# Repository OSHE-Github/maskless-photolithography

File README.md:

# Maskless Photolithography

*･゜ﾟ･*:.｡..｡.:*･'(*ﾟ▽ﾟ*)'･*:.｡. .｡.:*･゜ﾟ･*

## Copyright

- All code is licensed under the GPL 3.0 or later. You can view a copy of this license in LICENSE.code
- All hardware computer aided design "CAD files" are licensed under the CERN-OHL-S license. A copy of this license can be found in LICENSE.cad
- Some footprints are provided by the manufacturer or a third party source. They are licensed under their respective licenses.

Which licenses apply to which files will be clarified in a later commit. If you have questions please contact us.

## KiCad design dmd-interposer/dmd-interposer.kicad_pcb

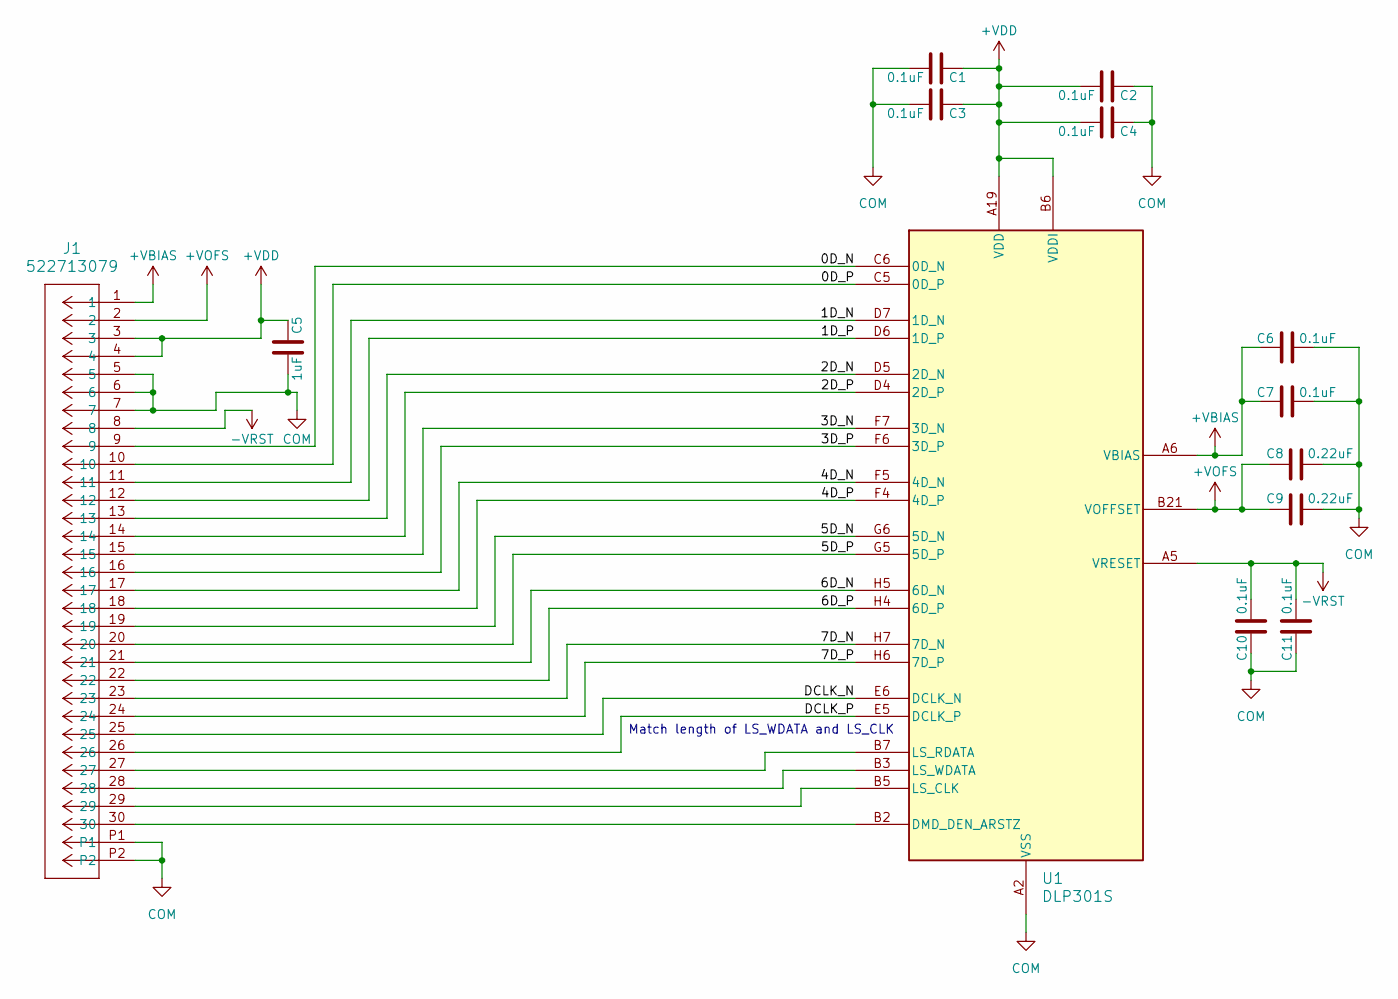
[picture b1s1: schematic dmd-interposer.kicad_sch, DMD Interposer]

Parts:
C1, C2, C3, C4, C6, C7, C10, C11: 0.1uF; C_0603_1608Metric_Pad1.08x0.95mm_HandSolder; Digikey 4713-GMC10X7R104K50NTCT-ND
C5: 1uF; C_0603_1608Metric_Pad1.08x0.95mm_HandSolder; Digikey 1276-1946-1-ND
C8, C9: 0.22uF; C_0805_2012Metric_Pad1.18x1.45mm_HandSolder; Digikey 1276-CL21B224KBFNNNFCT-ND
J1: 522713079; CON_522713079_MOL
U1: DLP301S; PCB_OUTLINE_DLP301S_INTERPOSER

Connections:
+VBIAS: C6.1, C7.1, J1.1, U1.A6 (VBIAS), U1.A22 (VBIAS)
+VDD: C1.1, C2.2, C3.1, C4.2, C5.1, J1.3, J1.4, U1.A19 (VDD), U1.A20 (VDD), U1.A21 (VDD), U1.B6 (VDDI), U1.B19 (VDDI), U1.B20 (VDD), U1.C2 (VDD), U1.C3 (VDDI), U1.C23 (VDDI), U1.D2 (VDD), U1.D3 (VDD), U1.D23 (VDD), U1.E2 (VDD), U1.E3 (VDDI), U1.E23 (VDDI), U1.F2 (VDD), U1.F3 (VDD), U1.F23 (VDD), U1.G3 (VDDI), U1.G23 (VDDI)
+VOFS: C8.2, C9.2, J1.2, U1.B21 (VOFFSET), U1.G2 (VOFFSET)
-VRST: C10.2, C11.2, J1.8, U1.A5 (VRESET), U1.A23 (VRESET)
/0D_N: J1.9, U1.C6 (0D_N)
/0D_P: J1.10, U1.C5 (0D_P)
/1D_N: J1.11, U1.D7 (1D_N)
/1D_P: J1.12, U1.D6 (1D_P)
/2D_N: J1.13, U1.D5 (2D_N)
/2D_P: J1.14, U1.D4 (2D_P)
/3D_N: J1.15, U1.F7 (3D_N)
/3D_P: J1.16, U1.F6 (3D_P)
/4D_N: J1.17, U1.F5 (4D_N)
/4D_P: J1.18, U1.F4 (4D_P)
/5D_N: J1.19, U1.G6 (5D_N)
/5D_P: J1.20, U1.G5 (5D_P)
/6D_N: J1.21, U1.H5 (6D_N)
/6D_P: J1.22, U1.H4 (6D_P)
/7D_N: J1.23, U1.H7 (7D_N)
/7D_P: J1.24, U1.H6 (7D_P)
/DCLK_N: J1.25, U1.E6 (DCLK_N)
/DCLK_P: J1.26, U1.E5 (DCLK_P)
COM: C1.2, C2.1, C3.2, C4.1, C5.2, C6.2, C7.2, C8.1, C9.1, C10.1, C11.1, J1.5, J1.6, J1.7, J1.P1, J1.P2, U1.A2 (VSS), U1.A3 (VSS), U1.A4 (VSS), U1.A7 (VSS), U1.A24 (VSS), U1.B22 (VSS), U1.B23 (VSS), U1.B24 (VSS), U1.C4 (VSS), U1.C7 (VSS), U1.C19 (VSS), U1.C22 (VSS), U1.E4 (VSS), U1.E7 (VSS), U1.E19 (VSS), U1.E22 (VSS), U1.G4 (VSS), U1.G7 (VSS), U1.G19 (VSS), U1.G22 (VSS), U1.G24 (VSS), U1.H2 (VSS), U1.H3 (VSS), U1.H23 (VSS), U1.H24 (VSS)
unnamed: J1.30, U1.B2 (DMD_DEN_ARSTZ)
unnamed: J1.29, U1.B5 (LS_CLK)
unnamed: J1.27, U1.B7 (LS_RDATA)
unnamed: J1.28, U1.B3 (LS_WDATA)

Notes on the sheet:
Match length of LS_WDATA and LS_CLK

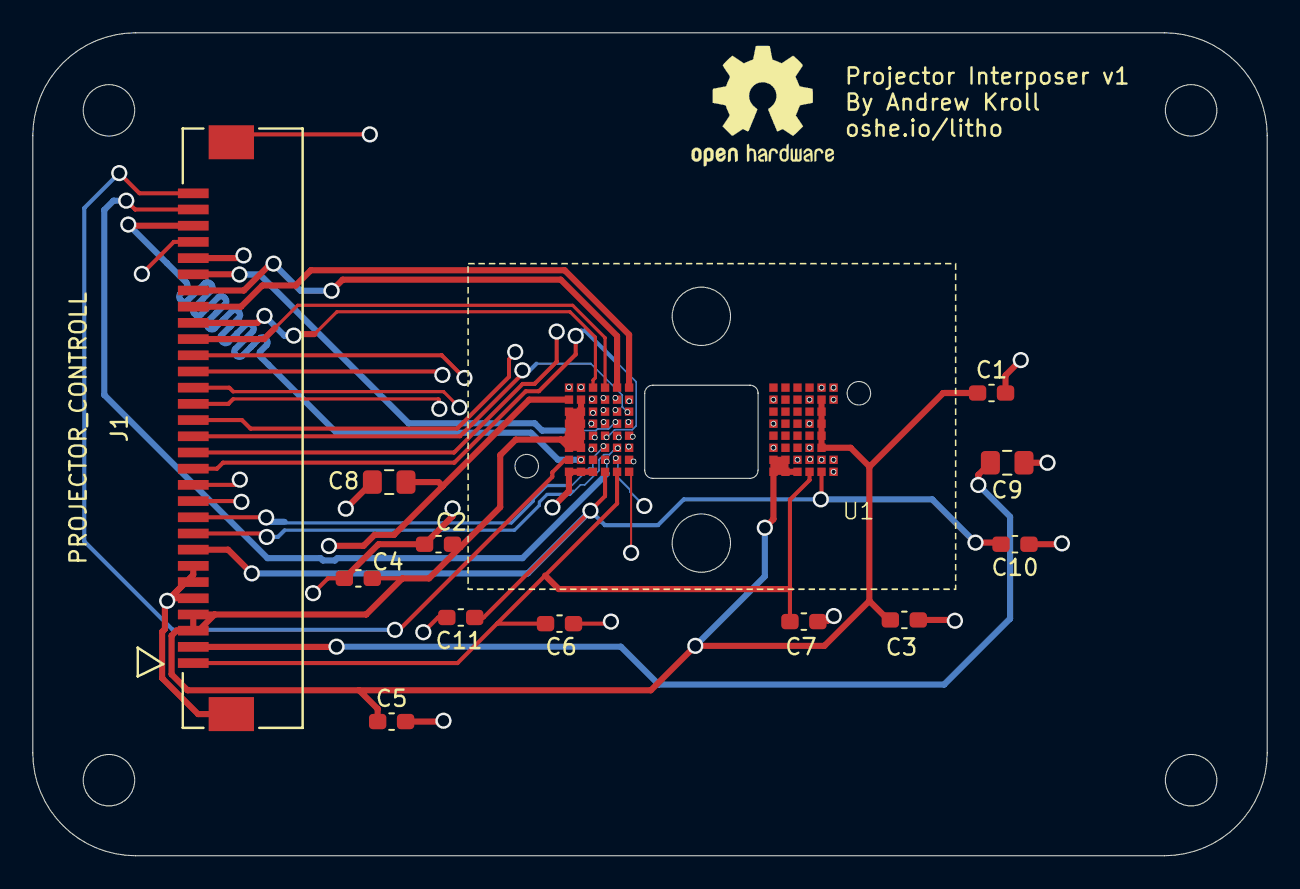
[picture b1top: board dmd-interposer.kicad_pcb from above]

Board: 4 copper layers, 76.2 x 50.8 mm, 13 parts (0 on the bottom side), 27 nets.

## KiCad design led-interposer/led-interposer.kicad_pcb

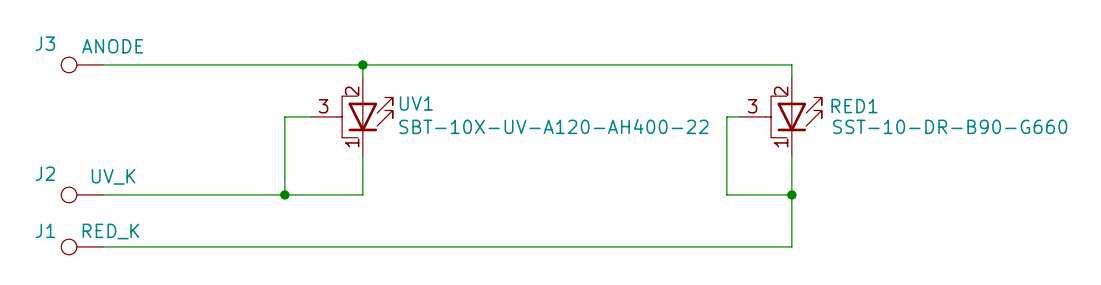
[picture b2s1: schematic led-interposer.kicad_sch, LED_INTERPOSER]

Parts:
J1: RED_K; TespointBig
J2: UV_K; TespointBig
J3: ANODE; TespointBig
RED1: SST-10-DR-B90-G660; LED_SST-10-DR-B90-G660; Digikey 1214-1436-1-ND
UV1: SBT-10X-UV-A120-AH400-22; LED_SBT-10X-UV-A120-AH400-22; Digikey 1214-SBT-10X-UV-A120-AH400-22CT-ND

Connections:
unnamed: J3.1 (1_1), RED1.2 (A), UV1.2 (A)
unnamed: J1.1 (1_1), RED1.1 (K), RED1.3 (PAD)
unnamed: J2.1 (1_1), UV1.1 (K), UV1.3 (PAD)

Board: 2 copper layers, 5 parts (0 on the bottom side), 3 nets, no tracks yet.
